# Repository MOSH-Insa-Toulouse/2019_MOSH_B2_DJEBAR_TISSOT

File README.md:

# Rendu MOSH/KICAD DJEBAR-TISSOT
## KICAD

Dans l'optique d'avoir un circuit optimal entre le module LoRa et le capteur de gaz présentés dans la partie MOSH ci-dessus, nous avons réalisé un shield qui dans l'idéal permettrait de pouvoir directement connecter notre capteur et notre émetteur de manière simplifiée.

Pour le schéma électrique, nous avons crée un composant représentant notre capteur de gaz et nous nous sommes basé sur ce que nous avons vu en cours :

Une fois le schéma électrique réalisé, il faut placer les différents composant sur le shield et les relier entre eux avec des pistes. C'est une partie complexe car il y'a beaucoup de contraintes à prendre en compte comme l'agencement des composants ou le fait que l'on puisse créer nos vias des deux cotés du shield.

Une fois ces deux parties réalisées (schéma électrique et agencement), on peut visualiser notre modèle 3D final.

## MOSH

#### I/ Les TPs

Après la présentation du cours par l’enseignant, nous avons décidé de commencer les Tps. Nous avons donc réalisé les activités des Tp 1 et 2 qui consistent surtout à réaliser le montage électrique nécessaire puis à téléverser le code fourni sur le moodle dans l’Arduino.
C’est un bon moyen de comprendre le fonctionnement de la carte Arduino à la fois au niveau du software mais aussi du hardware. 
De plus, certains montages peuvent nous pousser à être très créatifs comme celui du “Buzzer Melody” qui permet à tout le monde de créer sa propre mélodie. L’enseignant qui était également présent nous a aussi bien aidé

A partir du moment ou nous pensions maîtriser la carte, nous avons décidé de passer sur le mini projet.

#### II/ Le mini Projet

##### 1ère étape : Fabrication de l’émetteur/récepteur

La première étape fut de fabriquer l'émetteur/récepteur LoRa qui nous permettra par la suite de transmettre les données collectées par le capteur de gaz. Nous avions à notre disposition une puce RN 2483 permettant la communication LoRa et un support, sur lequel nous devions souder la puce. Afin de réaliser ce soudage, la lecture de la datasheet nous fut très utile et en particulier ce schéma :

A partir de ce schéma nous avons pu limiter le travail de soudage puisqu’il nous a permis de savoir de quels pins nous avions besoin. Il a également fallu souder l’antenne afin que le dispositif puisse fonctionner. 

Le résultat obtenu est le suivant :

##### 2ème étape : La mise en place

Une fois le module LoRa fabriqué, nous avons pu commencer à le faire fonctionner avec les branchements suivants :

 * RN2xx3 -- Arduino
 * Uart TX -- 10
 * Uart RX -- 11
 * Reset -- 12
 * Vcc -- 3.3V
 * Gnd -- Gnd

Nous avons d’abord communiqué en Serial chaque commande pour bien s’assurer que tout fonctionne, comme par exemple :  sys get hweui qui retourne l’adresse MAC du module.

Vous pourrez trouver le code utilisé en annexe.

##### 3ème étape : The Things Network

Afin de faire communiquer notre module LoRa précédemment validé, nous avons suivi le tutoriel présenté sur moodle afin de créer une application pour le capteur de gaz sur The Thing Networks. Nous avons donc utilisé le code joint en annexe, en utilisant une authentification ABP, puisque c’était la seule fonctionnelle.

Nous l’avons ensuite testé en générant des valeurs aléatoires afin de vérifier la bonne réception des données. 
On constate un petit délai ainsi que le besoin de réaliser l’affichage pour éviter un blocage au bout d’un certain nombre de données reçues.

##### 4ème étape : Réalisation d’un dashboard avec NodeRed

Afin de récupérer les données reçues sur The Things Network, il a fallu importer une bibliothèque pour avoir accès aux blocs permettant de récupérer ces valeurs.
Ensuite pour récupérer et traiter les données, il suffit de mettre en place ce type de graphes.

Inline-style: 

Les données ainsi récupérées peuvent ensuite être affichée sur sous forme de graphique, et on obtient ainsi le dashboard demandé.

##### Intégration avec le PCB conçu sur KiCad

Le PCB que nous avons crée avec le logiciel KiCad a pour vocation d'être utilisé conjointement avec ce que nous avons développé durant les séances de Mosh (code Arduino, dashboard...). Ce PCB est un shield qui se met par dessus l'arduino. Il permet ainsi d'utiliser directement le module Lora sans avoir à réaliser trop de branchements et permet d'acquérir les données issus du capteur de température que nous avons créé lors des séances d'AIME. 
Ainsi avec ce système, nous serions capable d'envoyer les donneés du capteur de gaz sur TTN en utilisant le réseau LoRa. On peut imaginer par la suite une multitude d'applications, par exemple une alarme pourrait être reliée au réseau TTN et se déclencher lorsqu'une valeur est estimée anormale.

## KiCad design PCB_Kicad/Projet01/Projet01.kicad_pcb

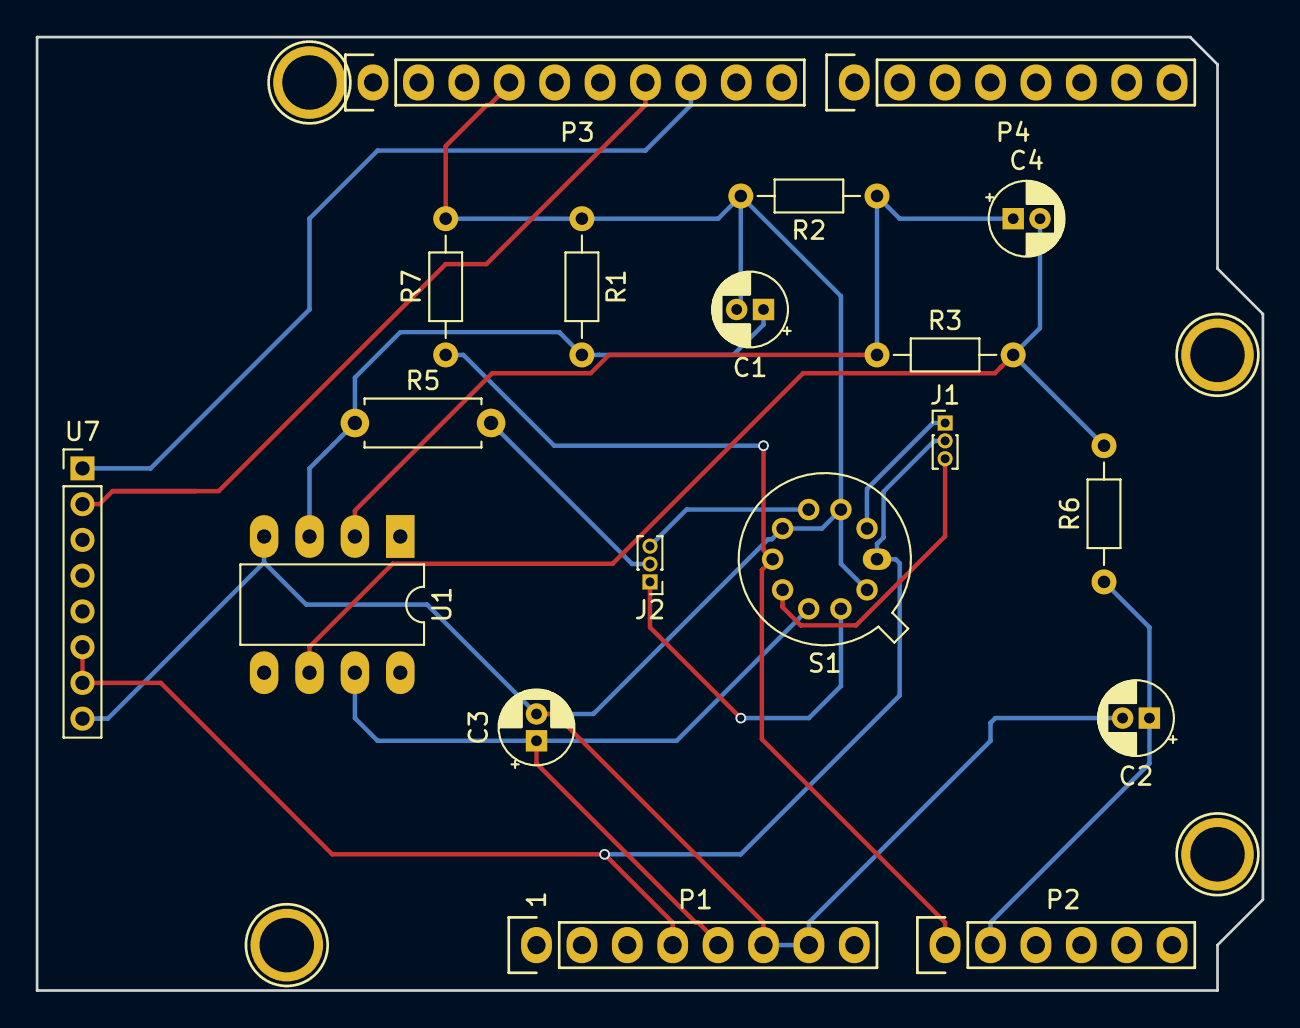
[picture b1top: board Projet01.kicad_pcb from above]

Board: 2 copper layers, 68.6 x 53.3 mm, 23 parts (0 on the bottom side), 15 nets.

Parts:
C1, C2, C3: 100n; CP_Radial_D4.0mm_P1.50mm
C4: 1µ; CP_Radial_D4.0mm_P1.50mm
J1, J2: SelectGazSensor; PinHeader_1x03_P1.00mm_Vertical
P1: Power; Socket_Strip_Arduino_1x08
P2: Analog; Socket_Strip_Arduino_1x06
P3: Digital; Socket_Strip_Arduino_1x10
P4: Digital; Socket_Strip_Arduino_1x08
P5, P6, P7, P8: CONN_01X01; Arduino_1pin
R1, R3: 100k; R_Axial_DIN0204_L3.6mm_D1.6mm_P7.62mm_Horizontal
R2, R6: 1k; R_Axial_DIN0204_L3.6mm_D1.6mm_P7.62mm_Horizontal
R5: 10k; R_Axial_DIN0207_L6.3mm_D2.5mm_P7.62mm_Horizontal
R7: R; R_Axial_DIN0204_L3.6mm_D1.6mm_P7.62mm_Horizontal
S1: Sensor_AIME; TO-5-10_Window
U1: LTC1050; DIP-8_W7.62mm_LongPads
U7: RN2483_Breakout; PinHeader_1x08_P2.00mm_Vertical

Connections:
+3V3: J1.2, P1.4, S1.1, U7.6, U7.7
+5V: C3.1, P1.5, S1.8, U1.7
/A0: P2.1, R7.1, S1.6
/A1: C2.1, P2.2, R6.1
/GazSensorLeft_pin2: J1.1, S1.2
/GazSensorLeft_pin4: J2.3, S1.4
/GazSensorRight_pin7: J1.3, S1.7
/GazSensorRight_pin9: J2.1, S1.9
/RX: P3.7, U7.2
/Rsens: J2.2, R5.2
/TX: P3.8, U7.1
GND: C1.2, C2.2, C3.2, P1.6, P1.7, P3.4, R1.1, R2.2, R7.2, S1.3, S1.5, S1.10, U1.4, U7.8
unnamed: C1.1, R1.2, R5.1, U1.3
unnamed: C4.1, R2.1, R3.1, U1.2
unnamed: C4.2, R3.2, R6.2, U1.6

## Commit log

2020-01-18 Transfert
2020-01-21 Reorganisation
2020-01-21 suppr
2020-01-21 Rename arduino_code.txt to arduino_code.ino
2020-01-22 Modification des urls des images
